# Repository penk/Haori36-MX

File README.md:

## Haori36-MX - 36-Key Split Monoblock Ortholinear Keyboard

Another no-frills build with per-key RGB LEDs, based on the [Choc version](https://github.com/penk/Haori36).

## Bill of Materials (BOM)

Quantity | Item
--- | ---
1 | RP2040-Zero
1 | Haori36-MX PCB
36 | MX switches and keycaps 
36 | MX Hotswap sockets
36 | 1N4148SOD-123 diodes
36 | SK6812MINI-E RGB LEDs
1 | Haori36-MX tray & plate
8 | M2×3 heat-set threaded inserts
8 | M2×8 countersunk screws

## Production Files

To place an order for the Haori36-MX PCB:

- Use the Gerber files available in the [production/](production/) folder.
- The [BOM](production/BOM.csv) and [CPL](production/CPL.csv) files can optionally be used with a PCBA service —— especially if you'd prefer to avoid soldering small diodes or LEDs. 😊

All components (except the MCU) are soldered to the back (bottom) side of the board.

The complete PCB design project is available in the [kicad/](kicad/) folder.

## 3D Printable Files

Print the case and plate using the provided [STL files](case/).

## Firmware

Precompiled VIA-enabled firmware:

- Flash `penk_haori36_mx_default.uf2` under [firmware/](firmware/) to the RP2040 MCU.
- Load the [via.json](firmware/QMK/keyboards/penk/haori36_mx/via.json) file in the `Design` tab for [VIA](https://usevia.app) configuration.

The QMK source is available under [firmware/QMK/keyboards/penk/haori36_mx](firmware/QMK/keyboards/penk/haori36_mx/).

### Default Keymaps 

The keymap is based on Rico's [rsta layout](https://github.com/rstacruz/my_qmk_keymaps/blob/main/preview.png), and the custom keycaps are made by FK Keycaps. 

You can order the same keycap set or customize yours at [https://fkcaps.com/custom/D7829J](https://fkcaps.com/custom/D7829J).

## Copyright and License
Copyright (c) 2025 Penk Chen. All rights reserved.

All files are licensed under the MIT license. For more information, see the [LICENSE](LICENSE).

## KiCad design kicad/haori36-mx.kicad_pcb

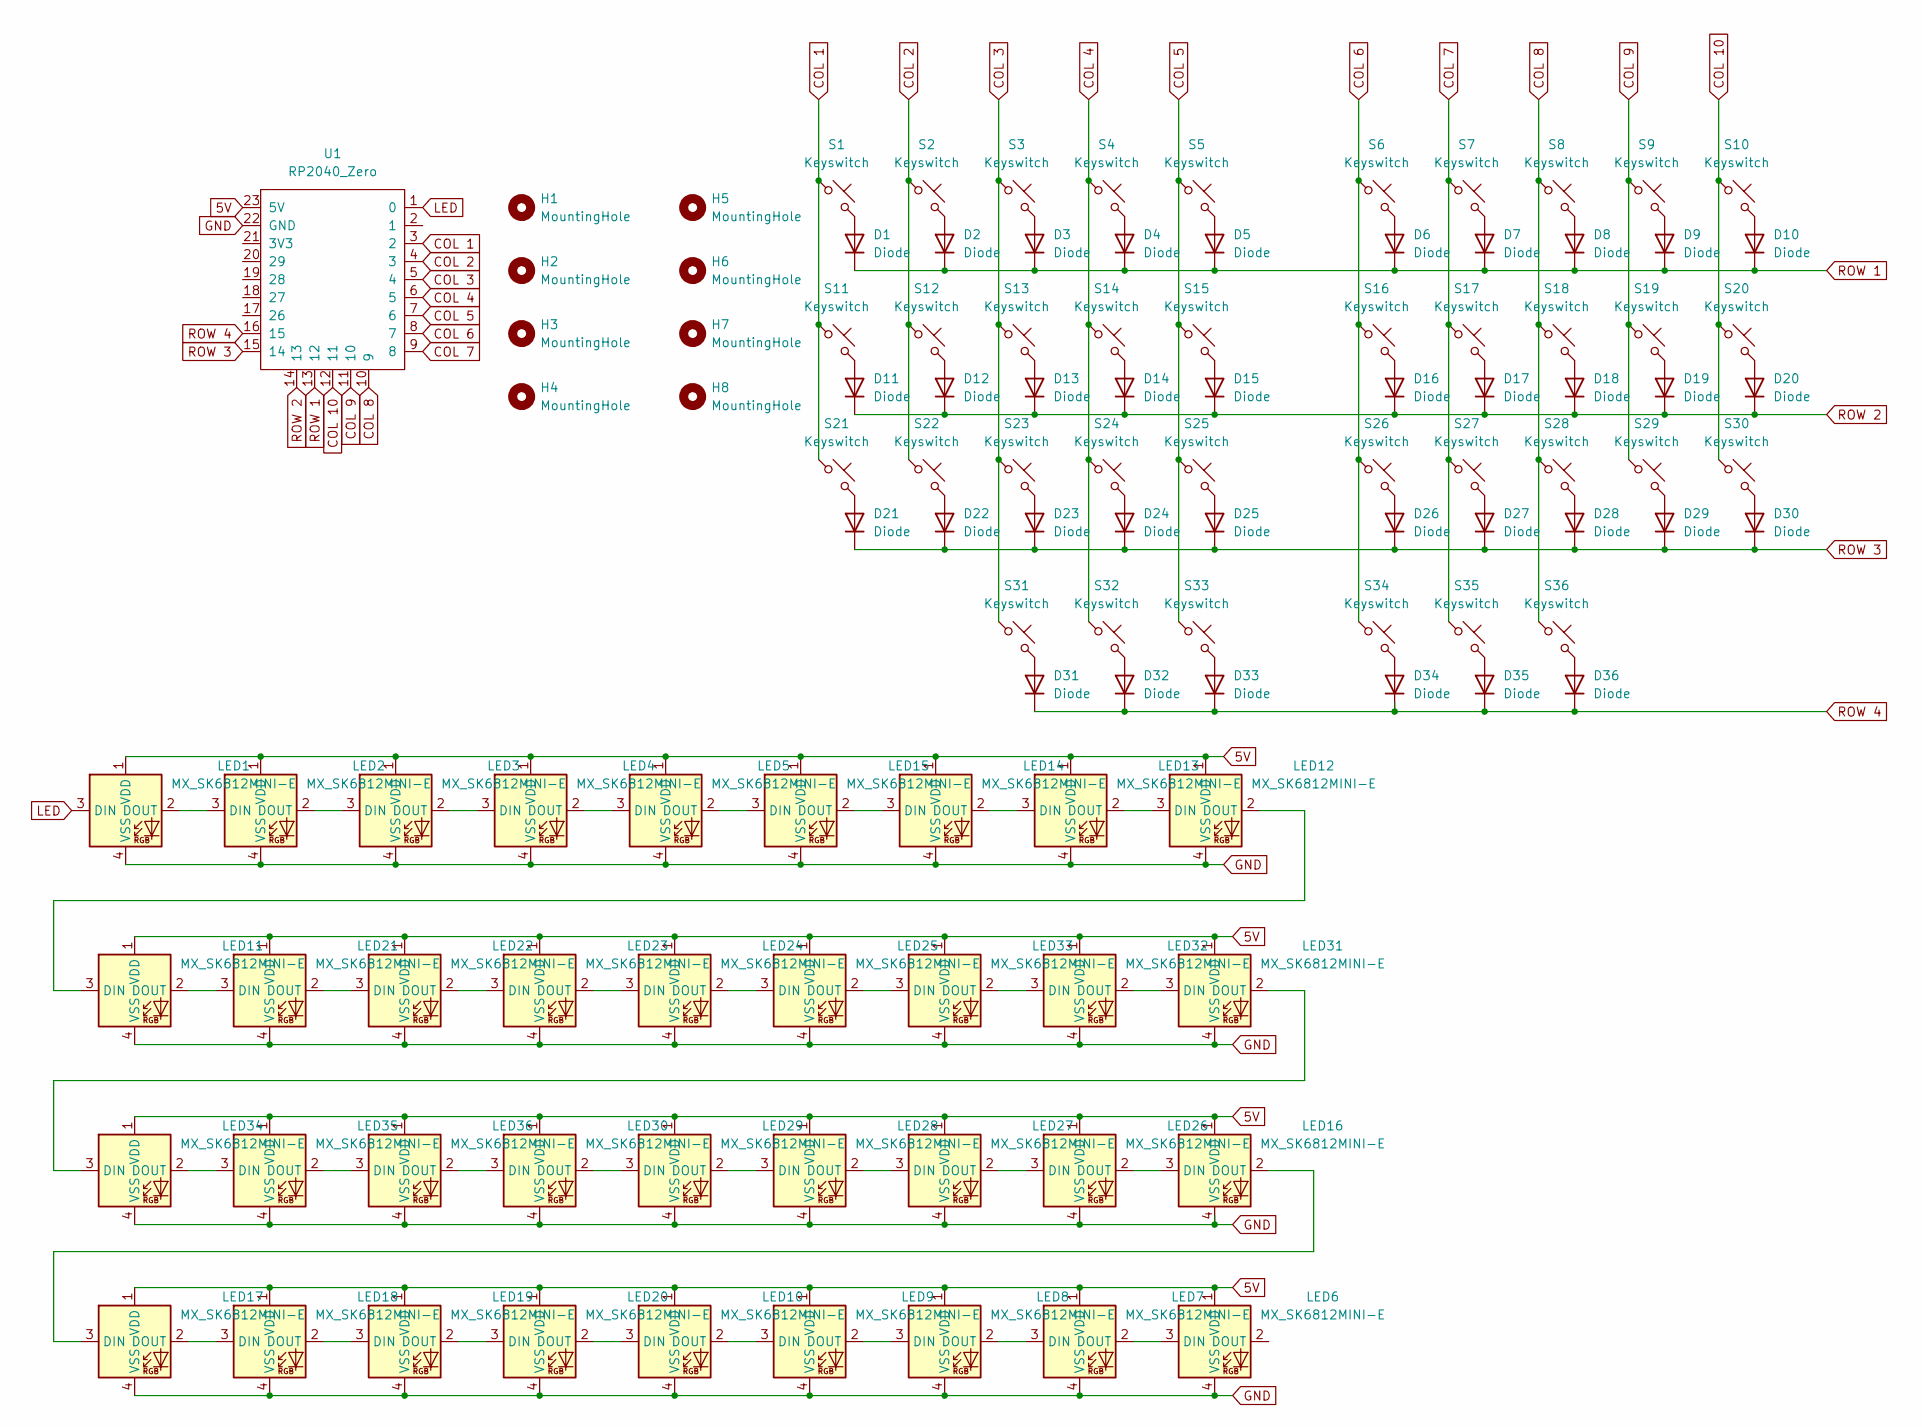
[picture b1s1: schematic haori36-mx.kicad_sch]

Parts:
D1, D2, D3, D4, D5, D6, D7, D8, D9, D10, D11, D12, D13, D14, D15, D16, D17, D18, D19, D20, D21, D22, D23, D24, D25, D26, D27, D28, D29, D30, D31, D32, D33, D34, D35, D36: Diode; Diode_SOD-123
H1, H2, H3, H4, H5, H6, H7, H8: MountingHole; MountingHole_2.2mm_M2
LED1, LED2, LED3, LED4, LED5, LED6, LED7, LED8, LED9, LED10, LED11, LED12, LED13, LED14, LED15, LED16, LED17, LED18, LED19, LED20, LED21, LED22, LED23, LED24, LED25, LED26, LED27, LED28, LED29, LED30, LED31, LED32, LED33, LED34, LED35, LED36: MX_SK6812MINI-E; LED_MX_6028R
S1, S2, S3, S4, S5, S6, S7, S8, S9, S10, S11, S12, S13, S14, S15, S16, S17, S18, S19, S20, S21, S22, S23, S24, S25, S26, S27, S28, S29, S30, S31, S32, S33, S34, S35, S36: Keyswitch; SW_MX_HS_CPG151101S11_1u
U1: RP2040_Zero; RP2040_Zero_holes

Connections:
5V: LED1.1 (VDD), LED2.1 (VDD), LED3.1 (VDD), LED4.1 (VDD), LED5.1 (VDD), LED6.1 (VDD), LED7.1 (VDD), LED8.1 (VDD), LED9.1 (VDD), LED10.1 (VDD), LED11.1 (VDD), LED12.1 (VDD), LED13.1 (VDD), LED14.1 (VDD), LED15.1 (VDD), LED16.1 (VDD), LED17.1 (VDD), LED18.1 (VDD), LED19.1 (VDD), LED20.1 (VDD), LED21.1 (VDD), LED22.1 (VDD), LED23.1 (VDD), LED24.1 (VDD), LED25.1 (VDD), LED26.1 (VDD), LED27.1 (VDD), LED28.1 (VDD), LED29.1 (VDD), LED30.1 (VDD), LED31.1 (VDD), LED32.1 (VDD), LED33.1 (VDD), LED34.1 (VDD), LED35.1 (VDD), LED36.1 (VDD), U1.23 (5V)
COL 1: S1.1, S11.1, S21.1, U1.3 (2)
COL 2: S2.1, S12.1, S22.1, U1.4 (3)
COL 3: S3.1, S13.1, S23.1, S31.1, U1.5 (4)
COL 4: S4.1, S14.1, S24.1, S32.1, U1.6 (5)
COL 5: S5.1, S15.1, S25.1, S33.1, U1.7 (6)
COL 6: S6.1, S16.1, S26.1, S34.1, U1.8 (7)
COL 7: S7.1, S17.1, S27.1, S35.1, U1.9 (8)
COL 8: S8.1, S18.1, S28.1, S36.1, U1.10 (9)
COL 9: S9.1, S19.1, S29.1, U1.11 (10)
COL 10: S10.1, S20.1, S30.1, U1.12 (11)
GND: LED1.4 (VSS), LED2.4 (VSS), LED3.4 (VSS), LED4.4 (VSS), LED5.4 (VSS), LED6.4 (VSS), LED7.4 (VSS), LED8.4 (VSS), LED9.4 (VSS), LED10.4 (VSS), LED11.4 (VSS), LED12.4 (VSS), LED13.4 (VSS), LED14.4 (VSS), LED15.4 (VSS), LED16.4 (VSS), LED17.4 (VSS), LED18.4 (VSS), LED19.4 (VSS), LED20.4 (VSS), LED21.4 (VSS), LED22.4 (VSS), LED23.4 (VSS), LED24.4 (VSS), LED25.4 (VSS), LED26.4 (VSS), LED27.4 (VSS), LED28.4 (VSS), LED29.4 (VSS), LED30.4 (VSS), LED31.4 (VSS), LED32.4 (VSS), LED33.4 (VSS), LED34.4 (VSS), LED35.4 (VSS), LED36.4 (VSS), U1.22 (GND)
LED: LED1.3 (DIN), U1.1 (0)
unnamed: D1.2 (A), S1.2
unnamed: D2.2 (A), S2.2
unnamed: D3.2 (A), S3.2
unnamed: D4.2 (A), S4.2
unnamed: D5.2 (A), S5.2
unnamed: D6.2 (A), S6.2
unnamed: D7.2 (A), S7.2
unnamed: D8.2 (A), S8.2
unnamed: D9.2 (A), S9.2
unnamed: D10.2 (A), S10.2
unnamed: D11.2 (A), S11.2
unnamed: D12.2 (A), S12.2
unnamed: D13.2 (A), S13.2
unnamed: D14.2 (A), S14.2
unnamed: D15.2 (A), S15.2
unnamed: D16.2 (A), S16.2
unnamed: D17.2 (A), S17.2
unnamed: D18.2 (A), S18.2
unnamed: D19.2 (A), S19.2
unnamed: D20.2 (A), S20.2
unnamed: D21.2 (A), S21.2
unnamed: D22.2 (A), S22.2
unnamed: D23.2 (A), S23.2
unnamed: D24.2 (A), S24.2
unnamed: D25.2 (A), S25.2
unnamed: D26.2 (A), S26.2
unnamed: D27.2 (A), S27.2
unnamed: D28.2 (A), S28.2
unnamed: D29.2 (A), S29.2
unnamed: D30.2 (A), S30.2
unnamed: D31.2 (A), S31.2
unnamed: D32.2 (A), S32.2
unnamed: D33.2 (A), S33.2
unnamed: D34.2 (A), S34.2
unnamed: D35.2 (A), S35.2
unnamed: D36.2 (A), S36.2
unnamed: LED1.2 (DOUT), LED2.3 (DIN)
unnamed: LED2.2 (DOUT), LED3.3 (DIN)
unnamed: LED3.2 (DOUT), LED4.3 (DIN)
unnamed: LED4.2 (DOUT), LED5.3 (DIN)
unnamed: LED6.3 (DIN), LED7.2 (DOUT)
unnamed: LED7.3 (DIN), LED8.2 (DOUT)
unnamed: LED8.3 (DIN), LED9.2 (DOUT)
unnamed: LED10.3 (DIN), LED20.2 (DOUT)
unnamed: LED9.3 (DIN), LED10.2 (DOUT)
unnamed: LED11.3 (DIN), LED12.2 (DOUT)
unnamed: LED11.2 (DOUT), LED21.3 (DIN)
unnamed: LED12.3 (DIN), LED13.2 (DOUT)
unnamed: LED13.3 (DIN), LED14.2 (DOUT)
unnamed: LED14.3 (DIN), LED15.2 (DOUT)
unnamed: LED5.2 (DOUT), LED15.3 (DIN)
unnamed: LED16.3 (DIN), LED26.2 (DOUT)
unnamed: LED16.2 (DOUT), LED17.3 (DIN)
unnamed: LED17.2 (DOUT), LED18.3 (DIN)
unnamed: LED18.2 (DOUT), LED19.3 (DIN)
unnamed: LED19.2 (DOUT), LED20.3 (DIN)
unnamed: LED21.2 (DOUT), LED22.3 (DIN)
unnamed: LED22.2 (DOUT), LED23.3 (DIN)
unnamed: LED23.2 (DOUT), LED24.3 (DIN)
unnamed: LED24.2 (DOUT), LED25.3 (DIN)
unnamed: LED25.2 (DOUT), LED33.3 (DIN)
unnamed: LED26.3 (DIN), LED27.2 (DOUT)
unnamed: LED27.3 (DIN), LED28.2 (DOUT)
unnamed: LED28.3 (DIN), LED29.2 (DOUT)
unnamed: LED29.3 (DIN), LED30.2 (DOUT)
unnamed: LED30.3 (DIN), LED36.2 (DOUT)
unnamed: LED31.3 (DIN), LED32.2 (DOUT)
unnamed: LED31.2 (DOUT), LED34.3 (DIN)
unnamed: LED32.3 (DIN), LED33.2 (DOUT)
unnamed: LED34.2 (DOUT), LED35.3 (DIN)
unnamed: LED35.2 (DOUT), LED36.3 (DIN)
ROW 1: D1.1 (K), D2.1 (K), D3.1 (K), D4.1 (K), D5.1 (K), D6.1 (K), D7.1 (K), D8.1 (K), D9.1 (K), D10.1 (K), U1.13 (12)
ROW 2: D11.1 (K), D12.1 (K), D13.1 (K), D14.1 (K), D15.1 (K), D16.1 (K), D17.1 (K), D18.1 (K), D19.1 (K), D20.1 (K), U1.14 (13)
ROW 3: D21.1 (K), D22.1 (K), D23.1 (K), D24.1 (K), D25.1 (K), D26.1 (K), D27.1 (K), D28.1 (K), D29.1 (K), D30.1 (K), U1.15 (14)
ROW 4: D31.1 (K), D32.1 (K), D33.1 (K), D34.1 (K), D35.1 (K), D36.1 (K), U1.16 (15)

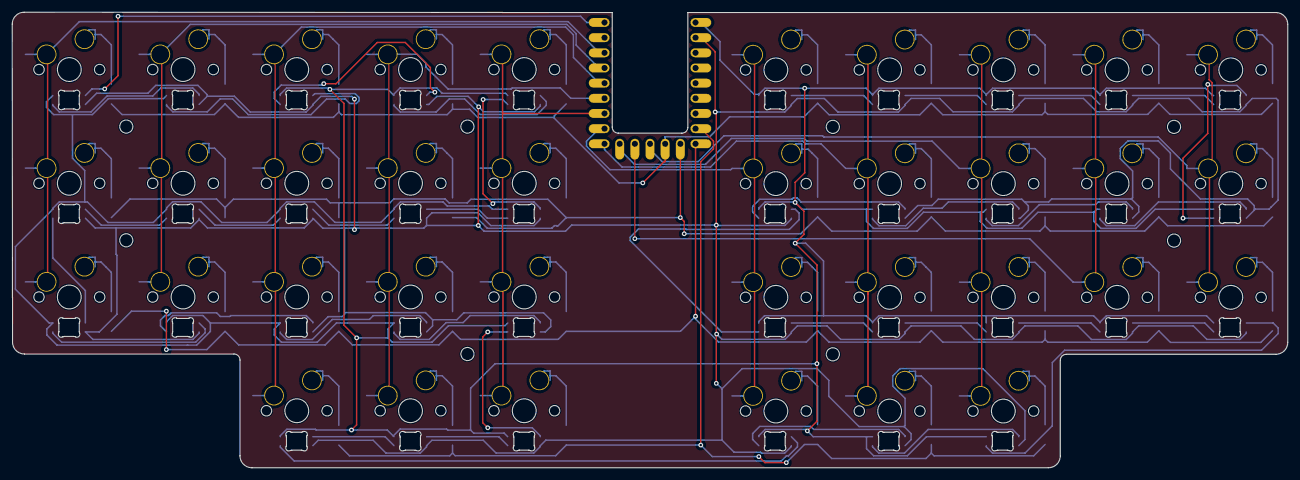
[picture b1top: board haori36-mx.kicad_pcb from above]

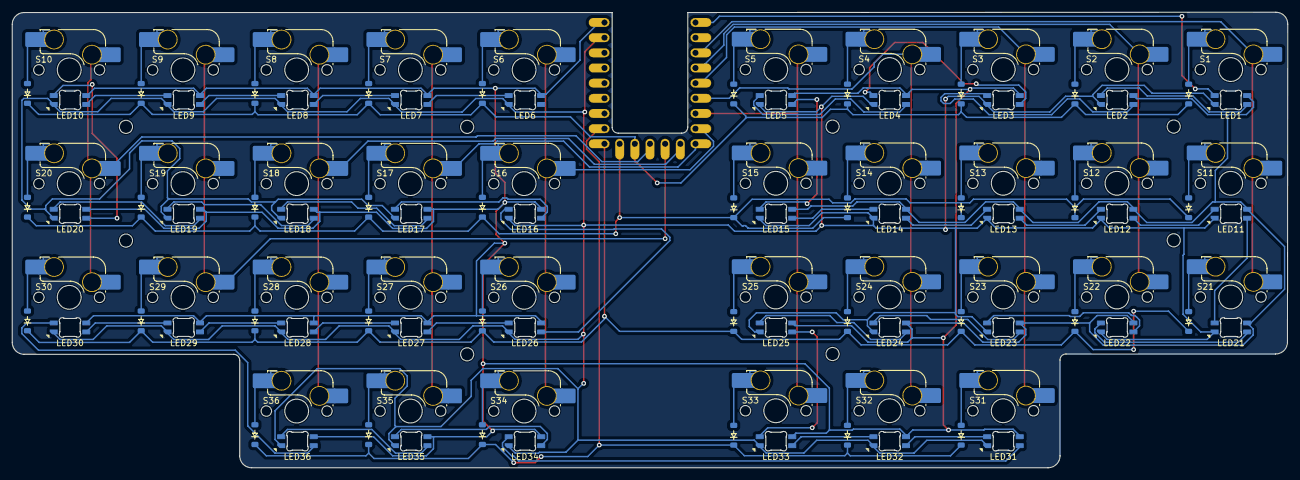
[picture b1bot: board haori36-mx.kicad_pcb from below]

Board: 2 copper layers, 213.6 x 76.3 mm, 117 parts (109 on the bottom side), 88 nets.

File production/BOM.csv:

Designator,Footprint,Quantity,Value,LCSC Part #
"D1, D10, D11, D12, D13, D14, D15, D16, D17, D18, D19, D2, D20, D21, D22, D23, D24, D25, D26, D27, D28, D29, D3, D30, D31, D32, D33, D34, D35, D36, D4, D5, D6, D7, D8, D9",Diode_SOD-123,36,Diode,C2972760
"LED1, LED10, LED11, LED12, LED13, LED14, LED15, LED16, LED17, LED18, LED19, LED2, LED20, LED21, LED22, LED23, LED24, LED25, LED26, LED27, LED28, LED29, LED3, LED30, LED31, LED32, LED33, LED34, LED35, LED36, LED4, LED5, LED6, LED7, LED8, LED9",LED_MX_6028R,36,MX_SK6812MINI-E,C5149201
"S1, S10, S11, S12, S13, S14, S15, S16, S17, S18, S19, S2, S20, S21, S22, S23, S24, S25, S26, S27, S28, S29, S3, S30, S31, S32, S33, S34, S35, S36, S4, S5, S6, S7, S8, S9",SW_MX_HS_CPG151101S11_1u,36,Keyswitch,C5156480
